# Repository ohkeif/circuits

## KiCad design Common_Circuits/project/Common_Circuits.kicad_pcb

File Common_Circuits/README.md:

# Common Circuits Keychain

Did you visit common circuits in Atlanta? And did you perhaps find yourself with a commemorative keychain accessory circuit board? After admiring the that commemorative keychain accessory circuit board for it's thoughtfulness, uniqueness, and clearly creative designer  - did you find yourself in a state of confounded intrigue as to the potential operation of the CKACB (commemorative keychain accessory circuit board)? Well you may be alone. Not that you are weird or slow or anything. It's just that I only made a few of these things...and I assume most people find them to be such a fashionable accessory, they may not even stop to think about the wonders that lie within the traces of their flashy keychain...but not you, you curious fellow. 

## What Dis Do?

All shall be revealed in due time...   

And that time is now. It's a synth. I mean it was pretty obvious to be honest..if you think about it. It's not like the event was for farming equipment or something. Then it maybe I could let it slide that you thought this was some sort of sprinkler timer. Or a controller to a door that automatically opens at sunrise to let the chickens out. The event was like 90% music oriented. You clearly already knew this. You are smart. Smart and Kind. And are just patiently waiting for the instructions on how do make it do a thing. The thing you knew it could do all along. Deep in your heart. And for that, I applaud you. And wait shall you no more!  

## But, I am not a Circuit Builder

Do not worry yourself with temporary concerns. And until you start on your learning journey, the CKACB will serve as a stylish keepsake of a truly memorable and life changing event for you. 

## BOM (Bill of Materials)

| Qty              | Reference | Value |
| :---------------- | :------: | ----: |
| 1	|C1	             | 0.01uf|
|1	|C2|	0.1uf|
|1	|C3	|10uf|
|1	|D1	|LED|
|2	|FREQ, PULSEWIDTH|	1M|
|1	|PWR	|DC IN|
|1	|OUT	|Audio Out
|2	|R1, R2	|1K|
|1	|R3	|10K|
|1	|R4	|4.7K|
|1	|SW2	|ON/OFF|
|2	|U1, U2	|LM555|
|1	|VOLUME	|5K|

## Stepped Tone Generator

This circuit is based off Forest Mims III Stepped Tone Generator circuit. It bleeps, bloops, and otherwise generates 8-bit console sounds. Sounds like high pitched zipping lasers and spacey distorted rocket arcade engine sounds. The circuit consists of two of the ubiquitous 8-pin DIP IC, the 555 timer, and an assortment of resistors and capacitors. In operation, the first timer is wired as an astable multivibrator that acts as a frequency oscillator. The second is set up as a monostable multivibrator that acts as the pulse width modulation of the firs timer. In other words, the oscillator (555 timer 1) drives the monostable (555 timer 2), which emits square output pulses with a duration controlled by the pulse width potentiometer. The resulting stepped tones almost sound like magic as they jump through lo-fi notes similar to chromatic rising and falling of keys on a keyboard.

## Assembly Instructions
Organize all your components to match up with the BOM to ensure you have everything you need to get started! Begin placing all the components onto the top side of the board with their legs poking through to the other side. 

Looking at the capacitors, C1 is marked with "103", where C2 is marked with "104". These numbers equate to the capacitance values, 0.01uf and 0.1uf respectively. 
C3 is an electrolytic capacitor with a cylindrical shape. This capacitor is polarized, meaning it has a positive and negative side. Find the negative side with the white stripe and place it accordingly on the board. 

### Electrolytic Capacitor Polarity

R1 and R2 are both 1k ohm resistors with the color code: Brown, Black, Red. R1 acts as a current limiter for the LED. R2 and the Frequency potentiometer controls the frequency of the audio oscillator. R3 and R4 along with the 10uf electrolytic capacitor form a low-pass filter that cut's high end artifacts from the audio output. Pulse Width controls the output pulse duration of the monostable multivibrator. And it is possible to add a mono jack onto pin 5 of each 555 chip to enable CV (control voltage) inputs for both controls.

Solder the IC socket with the correct orientation onto the board. Keep note of the notch on one end. Insert the IC into the IC socket staying consistent with the notch. Or don't use a socket. Just be careful and give the chip some time to cool off between soldering pins if soldering sans socket. 

### IC and IC Socket

Finally, obtain some spools of wire (20-24 gauge stranded core) and wire up the potentiometers, switches and power connections. To keep things organized, it may help to use green wire for ground connections, red wire for 9v connections, and yellow wire for audio connections. 

Now you can tape down all the components and flip over the board to solder everything up! 

### Schematic

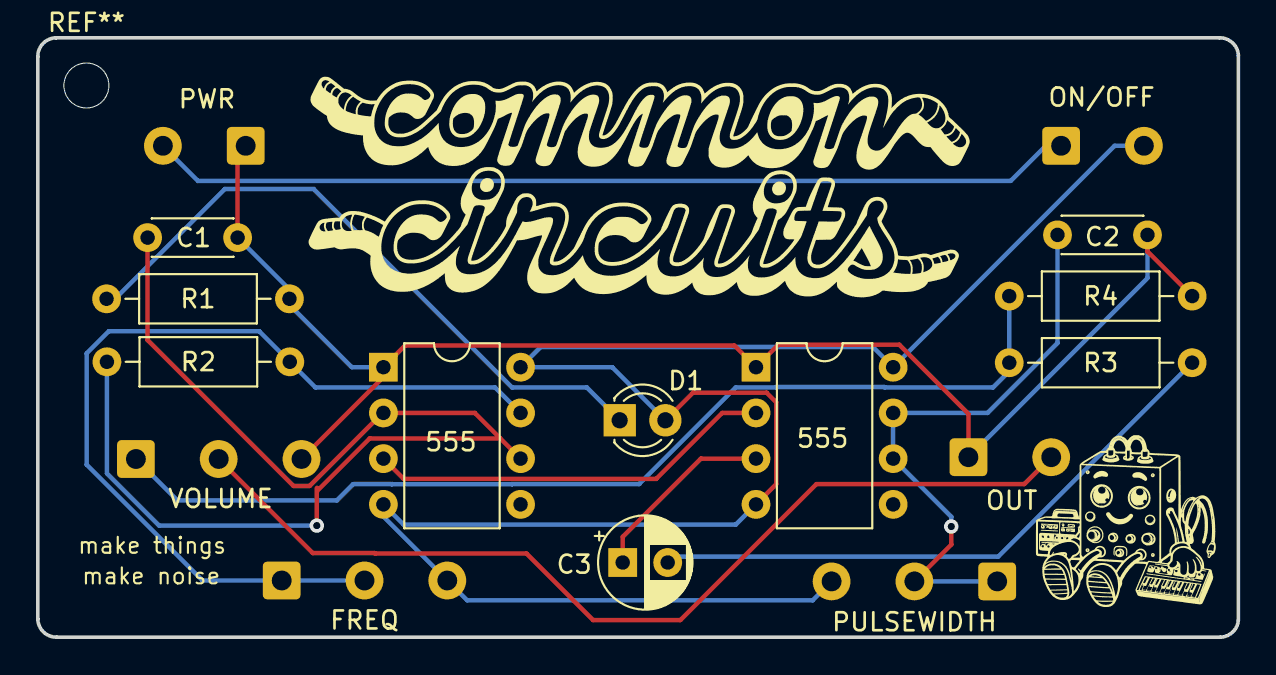
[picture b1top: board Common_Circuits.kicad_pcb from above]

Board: 2 copper layers, 66.7 x 33.3 mm, 16 parts (0 on the bottom side), 12 nets.

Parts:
C1: 0.01uf; C_Disc_D4.3mm_W1.9mm_P5.00mm
C2: 0.1uf; C_Disc_D4.3mm_W1.9mm_P5.00mm
C3: 10uf; CP_Radial_D5.0mm_P2.50mm
D1: LED; LED_D3.0mm
FREQ: 1M; SolderWire-0.5sqmm_1x03_P4.6mm_D0.9mm_OD2.1mm
ON/OFF: ON/OFF; SolderWire-0.5sqmm_1x02_P4.6mm_D0.9mm_OD2.1mm
OUT: Audio Out; SolderWire-0.5sqmm_1x02_P4.6mm_D0.9mm_OD2.1mm
PULSEWIDTH: 1M; SolderWire-0.5sqmm_1x03_P4.6mm_D0.9mm_OD2.1mm
PWR: DC IN; SolderWire-0.5sqmm_1x02_P4.6mm_D0.9mm_OD2.1mm
R1, R2: 1K; R_Axial_DIN0207_L6.3mm_D2.5mm_P10.16mm_Horizontal
R3: 10K; R_Axial_DIN0207_L6.3mm_D2.5mm_P10.16mm_Horizontal
R4: 4.7K; R_Axial_DIN0207_L6.3mm_D2.5mm_P10.16mm_Horizontal
U1, U2: 555; DIP-8_W7.62mm
VOLUME: 5K; SolderWire-0.5sqmm_1x03_P4.6mm_D0.9mm_OD2.1mm

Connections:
+9V: ON/OFF.1 (A), PWR.2
/PWR: D1.2 (A), FREQ.3, ON/OFF.2 (B), PULSEWIDTH.3, U1.4 (R), U1.8 (VCC), U2.4 (R), U2.8 (VCC)
GND: C1.1, C2.1, OUT.S, PWR.1, R1.1, R4.1, U1.1 (GND), U2.1 (GND), VOLUME.3
unnamed: C1.2, R2.2, U1.2 (TR), U1.6 (THR)
unnamed: D1.1 (K), R1.2
unnamed: FREQ.1, FREQ.2, R2.1, U1.7 (DIS)
unnamed: OUT.T, VOLUME.2
unnamed: C2.2, PULSEWIDTH.1, PULSEWIDTH.2, U2.6 (THR), U2.7 (DIS)
unnamed: C3.2, R3.1
unnamed: R3.2, R4.2, VOLUME.1
unnamed: U1.3 (Q), U2.2 (TR)
unnamed: C3.1, U2.3 (Q)

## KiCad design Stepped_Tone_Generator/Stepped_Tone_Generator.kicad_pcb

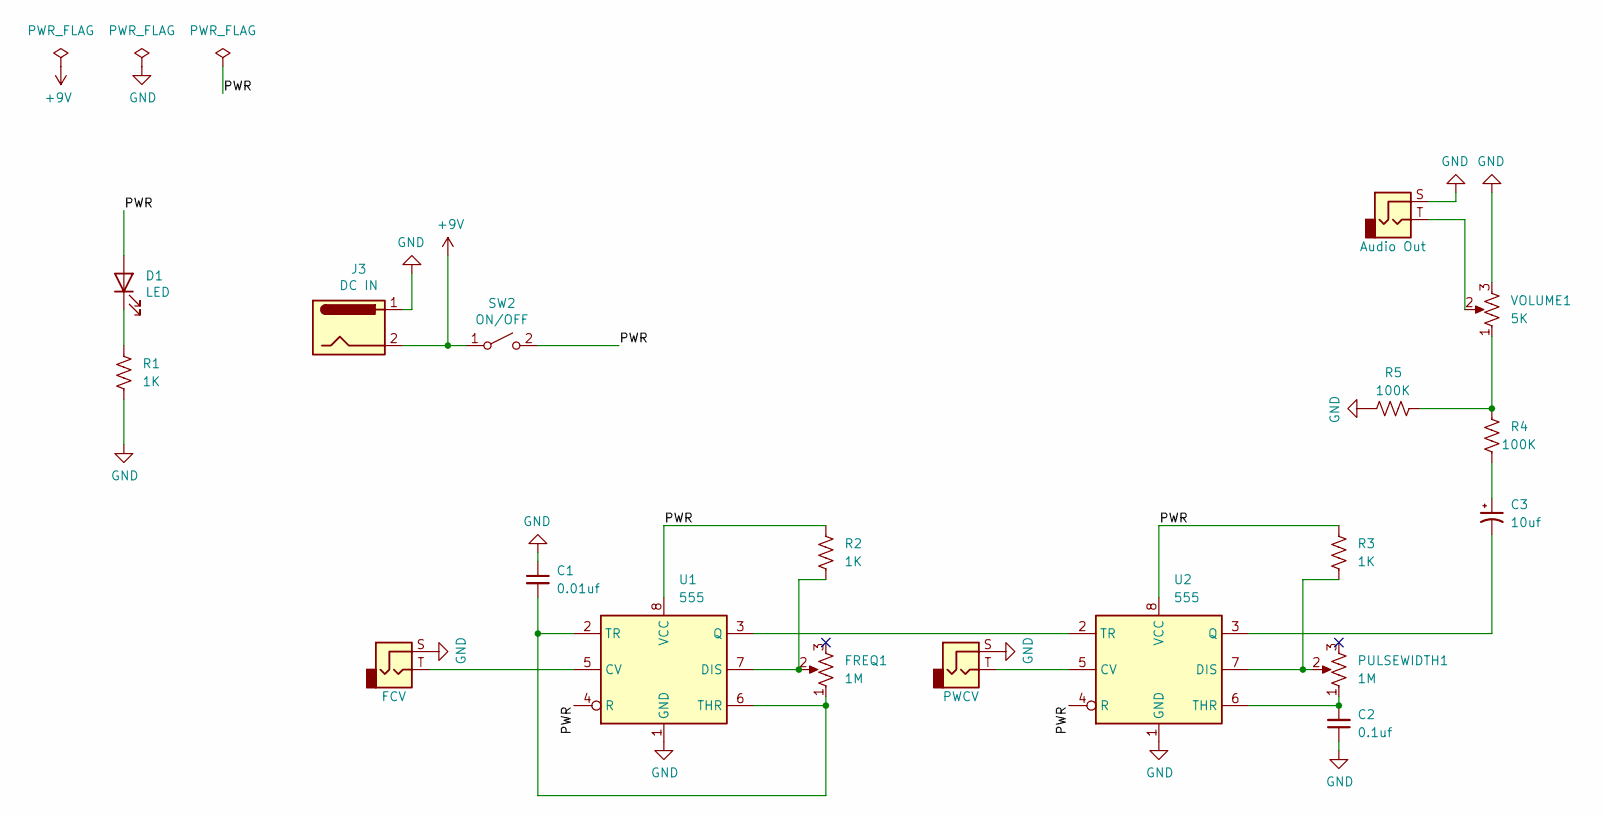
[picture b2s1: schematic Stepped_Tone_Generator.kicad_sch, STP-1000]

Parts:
C1: 0.01uf; C_Disc_D4.3mm_W1.9mm_P5.00mm
C2: 0.1uf; C_Disc_D4.3mm_W1.9mm_P5.00mm
C3: 10uf; CP_Radial_D5.0mm_P2.50mm
D1: LED; LED_D3.0mm
FREQ1: 1M; SolderWire-0.5sqmm_1x03_P4.6mm_D0.9mm_OD2.1mm
J1: FCV; SolderWire-0.5sqmm_1x02_P4.6mm_D0.9mm_OD2.1mm
J2: PWCV; SolderWire-0.5sqmm_1x02_P4.6mm_D0.9mm_OD2.1mm
J3: DC IN; SolderWire-0.5sqmm_1x02_P4.6mm_D0.9mm_OD2.1mm
J4: Audio Out; SolderWire-0.5sqmm_1x02_P4.6mm_D0.9mm_OD2.1mm
PULSEWIDTH1: 1M; SolderWire-0.5sqmm_1x03_P4.6mm_D0.9mm_OD2.1mm
R1, R2, R3: 1K; R_Axial_DIN0207_L6.3mm_D2.5mm_P10.16mm_Horizontal
R4, R5: 100K; R_Axial_DIN0207_L6.3mm_D2.5mm_P10.16mm_Horizontal
SW2: ON/OFF; SolderWire-0.5sqmm_1x02_P4.6mm_D0.9mm_OD2.1mm
U1, U2: 555; DIP-8_W7.62mm
VOLUME1: 5K; SolderWire-0.5sqmm_1x03_P4.6mm_D0.9mm_OD2.1mm

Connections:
+9V: J3.2, SW2.1 (A)
/PWR: D1.2 (A), R2.2, R3.2, SW2.2 (B), U1.4 (R), U1.8 (VCC), U2.4 (R), U2.8 (VCC)
GND: C1.1, C2.1, J1.S, J2.S, J3.1, J4.S, R1.1, R5.1, U1.1 (GND), U2.1 (GND), VOLUME1.3
unnamed: C1.2, FREQ1.1, U1.2 (TR), U1.6 (THR)
unnamed: C2.2, PULSEWIDTH1.1, U2.6 (THR)
unnamed: C3.1, R4.1
unnamed: C3.2, U2.3 (Q)
unnamed: D1.1 (K), R1.2
unnamed: FREQ1.2, R2.1, U1.7 (DIS)
unnamed: J1.T, U1.5 (CV)
unnamed: J2.T, U2.5 (CV)
unnamed: J4.T, VOLUME1.2
unnamed: PULSEWIDTH1.2, R3.1, U2.7 (DIS)
unnamed: R4.2, R5.2, VOLUME1.1
unnamed: U1.3 (Q), U2.2 (TR)

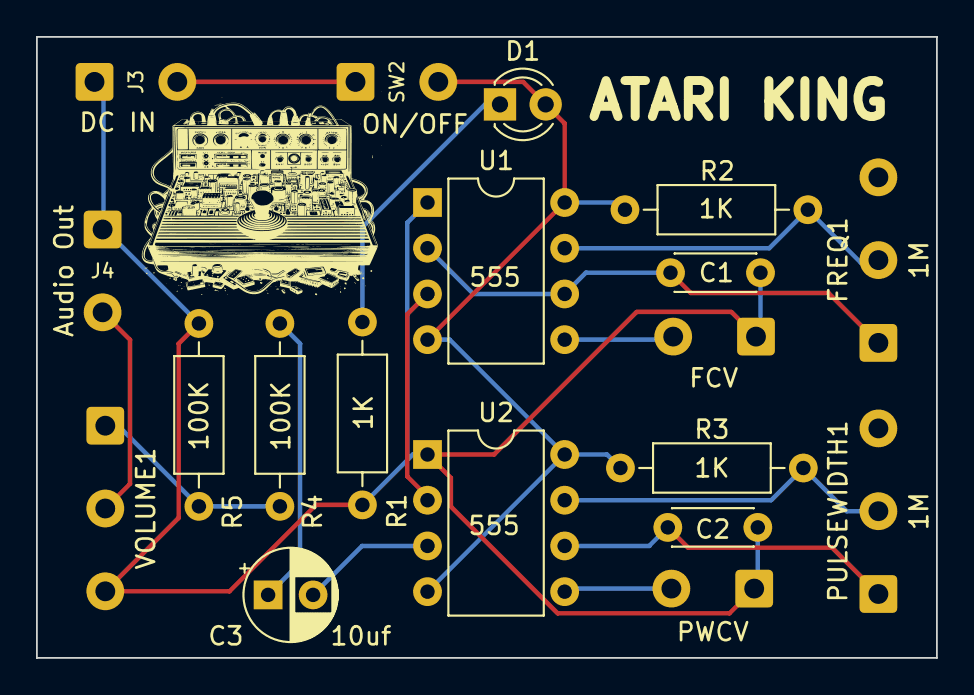
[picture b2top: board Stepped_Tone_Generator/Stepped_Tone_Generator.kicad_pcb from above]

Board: 2 copper layers, 50.0 x 34.5 mm, 19 parts (0 on the bottom side), 15 nets.

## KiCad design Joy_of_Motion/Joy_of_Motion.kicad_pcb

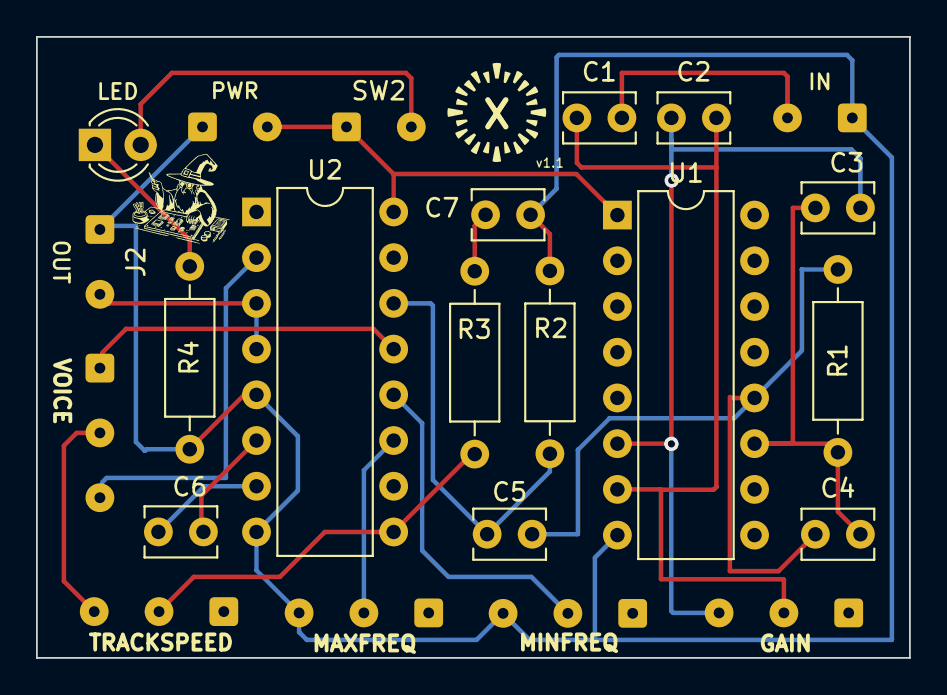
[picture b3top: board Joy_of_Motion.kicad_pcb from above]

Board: 2 copper layers, 48.5 x 34.5 mm, 23 parts (0 on the bottom side), 20 nets.

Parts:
C1, C3, C5, C6, C7: 0.1uf; C_Disc_D3.8mm_W2.6mm_P2.50mm
C2, C4: 47pf; C_Disc_D3.8mm_W2.6mm_P2.50mm
GAIN1: 1M; SolderWire-0.1sqmm_1x03_P3.6mm_D0.4mm_OD1mm
J1: IN; SolderWire-0.1sqmm_1x02_P3.6mm_D0.4mm_OD1mm
J2: OUT; SolderWire-0.1sqmm_1x02_P3.6mm_D0.4mm_OD1mm
LED: LED; LED_D3.0mm
MAXFREQ1: 1M; SolderWire-0.1sqmm_1x03_P3.6mm_D0.4mm_OD1mm
MINFREQ1: 1M; SolderWire-0.1sqmm_1x03_P3.6mm_D0.4mm_OD1mm
PWR: DC IN; SolderWire-0.1sqmm_1x02_P3.6mm_D0.4mm_OD1mm
R1, R2, R3: 100K; R_Axial_DIN0207_L6.3mm_D2.5mm_P10.16mm_Horizontal
R4: 1k; R_Axial_DIN0207_L6.3mm_D2.5mm_P10.16mm_Horizontal
SW1: VOICE; SolderWire-0.1sqmm_1x03_P3.6mm_D0.4mm_OD1mm
SW2: ON/OFF; SolderWire-0.1sqmm_1x02_P3.6mm_D0.4mm_OD1mm
TRKSPD1: 1M; SolderWire-0.1sqmm_1x03_P3.6mm_D0.4mm_OD1mm
U1: 4049; DIP-16_W7.62mm
U2: 4046; DIP-16_W7.62mm

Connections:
+9V: PWR.2, SW2.1 (A), U1.8 (VSS), U2.16 (VDD)
/PWR: LED.2 (A), SW2.2 (B)
GND: C5.1, J1.S, J2.S, MAXFREQ1.3, MINFREQ1.3, PWR.1, R3.1, R4.2, U1.1 (VCC), U2.5 (Inh), U2.8 (VSS)
unnamed: C1.1, C2.2, GAIN1.2, U1.7
unnamed: C1.2, J1.T
unnamed: C2.1, C3.2, GAIN1.3, U1.6
unnamed: C3.1, C4.2, R1.2, U1.11
unnamed: C4.1, C6.2, R1.1, U1.12
unnamed: C5.2, R2.2
unnamed: C6.1, R3.2, U2.14 (SigIn)
unnamed: C7.1, U2.7 (C2)
unnamed: C7.2, U2.6 (C1)
unnamed: LED.1 (K), R4.1
unnamed: J2.T, U2.3 (RefIn), U2.4 (FOUT)
unnamed: MAXFREQ1.2, U2.11 (R1)
unnamed: MINFREQ1.2, U2.12 (R2)
unnamed: R2.1, TRKSPD1.2, U2.9 (VCOin)
unnamed: SW1.1 (A), U2.13 (PC2)
unnamed: SW1.2 (B), TRKSPD1.3
unnamed: SW1.3 (C), U2.2 (PC1)

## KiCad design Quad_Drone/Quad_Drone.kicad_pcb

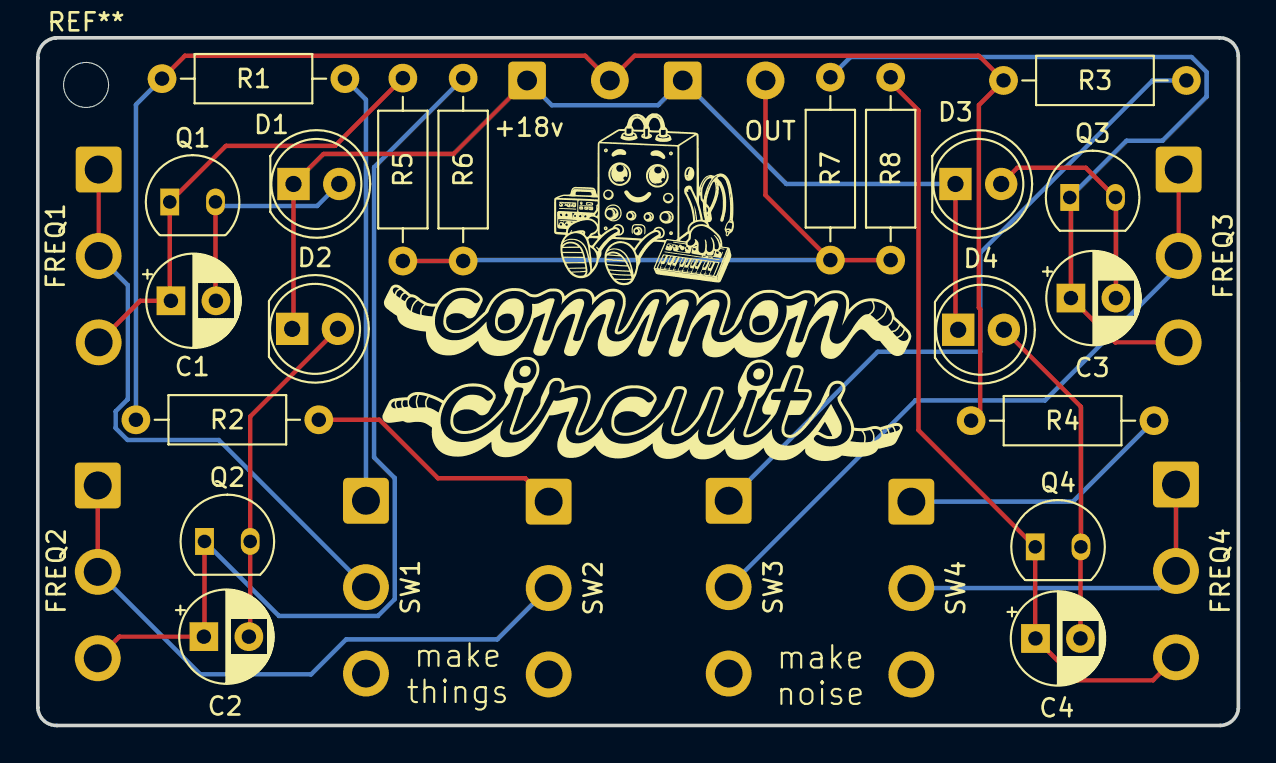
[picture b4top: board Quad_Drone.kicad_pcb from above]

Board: 2 copper layers, 66.7 x 38.2 mm, 30 parts (0 on the bottom side), 19 nets.

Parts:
+18v: DC IN; SolderWire-0.5sqmm_1x02_P4.6mm_D0.9mm_OD2.1mm
C1, C2: 10uf; CP_Radial_D5.0mm_P2.50mm
C3: 4.7uf; CP_Radial_D5.0mm_P2.50mm
C4: 2.2uf; CP_Radial_D5.0mm_P2.50mm
D1, D2, D3, D4: LED; LED_D5.0mm
FREQ1, FREQ2, FREQ3, FREQ4: 10k; SolderWire-0.75sqmm_1x03_P4.8mm_D1.25mm_OD2.3mm
OUT: OUT; SolderWire-0.5sqmm_1x02_P4.6mm_D0.9mm_OD2.1mm
Q1, Q2, Q3, Q4: 2N3904; TO-92-2-modified
R1, R2, R3, R4: 1K; R_Axial_DIN0207_L6.3mm_D2.5mm_P10.16mm_Horizontal
R5, R6, R7, R8: 100K; R_Axial_DIN0207_L6.3mm_D2.5mm_P10.16mm_Horizontal
SW1, SW2, SW3, SW4: ON/OFF; SolderWire-0.75sqmm_1x03_P4.8mm_D1.25mm_OD2.3mm

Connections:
+9V: +18v.2, R1.1, R2.1, R3.1, R4.1
GND: +18v.1, D1.1 (K), D2.1 (K), D3.1 (K), D4.1 (K), OUT.1
unnamed: C1.1, FREQ1.3, Q1.1 (E), R5.1
unnamed: C1.2, D1.2 (A), Q1.3 (C)
unnamed: C2.1, FREQ2.3, Q2.1 (E), R6.1
unnamed: C2.2, D2.2 (A), Q2.3 (C)
unnamed: C3.1, FREQ3.3, Q3.1 (E), R7.1
unnamed: C3.2, D3.2 (A), Q3.3 (C)
unnamed: C4.1, FREQ4.3, Q4.1 (E), R8.1
unnamed: C4.2, D4.2 (A), Q4.3 (C)
unnamed: FREQ1.1, FREQ1.2, SW1.2 (B)
unnamed: FREQ2.1, FREQ2.2, SW2.2 (B)
unnamed: FREQ3.1, FREQ3.2, SW3.2 (B)
unnamed: FREQ4.1, FREQ4.2, SW4.2 (B)
unnamed: OUT.T, R5.2, R6.2, R7.2, R8.2
unnamed: R1.2, SW1.1 (A)
unnamed: R2.2, SW2.1 (A)
unnamed: R3.2, SW3.1 (A)
unnamed: R4.2, SW4.1 (A)

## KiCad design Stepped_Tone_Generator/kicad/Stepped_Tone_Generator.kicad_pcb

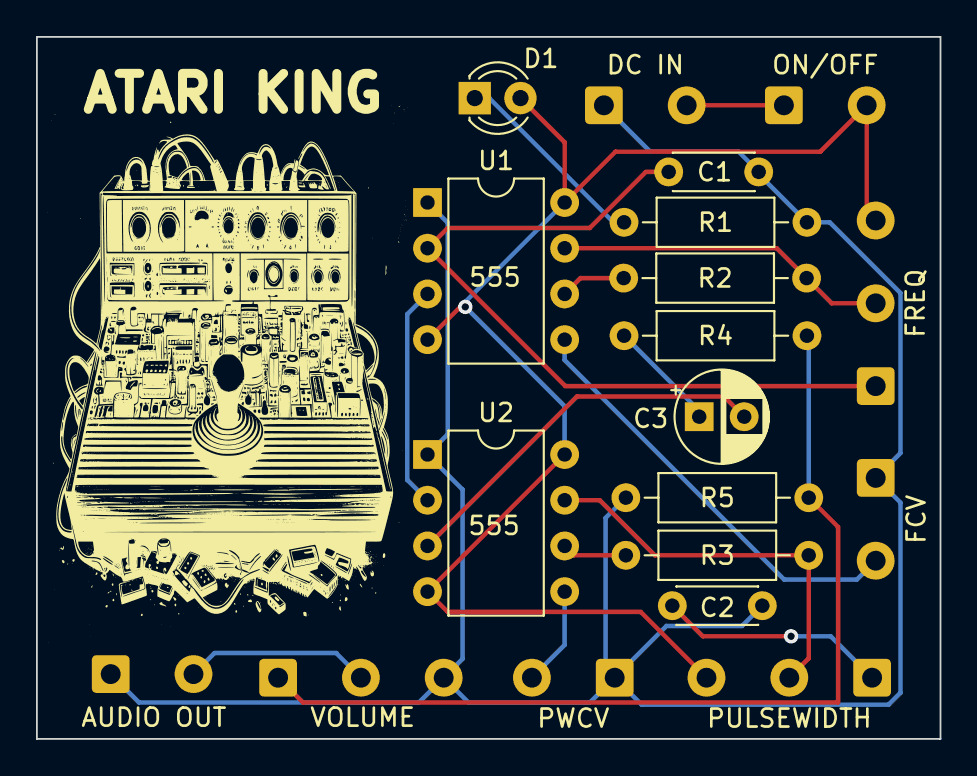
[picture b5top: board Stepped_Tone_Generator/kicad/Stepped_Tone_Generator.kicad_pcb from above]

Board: 2 copper layers, 50.2 x 39.0 mm, 19 parts (0 on the bottom side), 17 nets.

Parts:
AUDIO OUT: AUDIO OUT; SolderWire-0.5sqmm_1x02_P4.6mm_D0.9mm_OD2.1mm
C1: .01uf; C_Disc_D4.3mm_W1.9mm_P5.00mm
C2: .1uf; C_Disc_D4.3mm_W1.9mm_P5.00mm
C3: 10uf; CP_Radial_D5.0mm_P2.50mm
D1: LED; LED_D3.0mm
DC IN: DC IN; SolderWire-0.5sqmm_1x02_P4.6mm_D0.9mm_OD2.1mm
FCV: FCV; SolderWire-0.5sqmm_1x02_P4.6mm_D0.9mm_OD2.1mm
FREQ: 1M; SolderWire-0.5sqmm_1x03_P4.6mm_D0.9mm_OD2.1mm
ON/OFF: ON/OFF; SolderWire-0.5sqmm_1x02_P4.6mm_D0.9mm_OD2.1mm
PULSEWIDTH: 1M; SolderWire-0.5sqmm_1x03_P4.6mm_D0.9mm_OD2.1mm
PWCV: PWCV; SolderWire-0.5sqmm_1x02_P4.6mm_D0.9mm_OD2.1mm
R1, R2, R3: 1K; R_Axial_DIN0207_L6.3mm_D2.5mm_P10.16mm_Horizontal
R4: 10K; R_Axial_DIN0207_L6.3mm_D2.5mm_P10.16mm_Horizontal
R5: 4.7K; R_Axial_DIN0207_L6.3mm_D2.5mm_P10.16mm_Horizontal
U1, U2: 555; DIP-8_W7.62mm
VOLUME: 5K; SolderWire-0.5sqmm_1x03_P4.6mm_D0.9mm_OD2.1mm

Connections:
+9V: DC IN.2, ON/OFF.1 (A)
/PWR: D1.2 (A), FREQ.3, ON/OFF.2 (B), PULSEWIDTH.3, U1.4 (R), U1.8 (VCC), U2.4 (R), U2.8 (VCC)
GND: AUDIO OUT.S, C1.1, C2.1, DC IN.1, FCV.S, PWCV.S, R1.1, R5.1, U1.1 (GND), U2.1 (GND), VOLUME.3
unnamed: C1.2, FREQ.1, U1.2 (TR)
unnamed: C3.1, R4.1
unnamed: C3.2, U2.3 (Q)
unnamed: D1.1 (K), R1.2
unnamed: FREQ.2, R2.2, U1.7 (DIS)
unnamed: FCV.T, U1.5 (CV)
unnamed: PWCV.T, U2.5 (CV)
unnamed: AUDIO OUT.T, VOLUME.2
unnamed: C2.2, PULSEWIDTH.1
unnamed: PULSEWIDTH.2, R3.2, U2.7 (DIS)
unnamed: R4.2, R5.2, VOLUME.1
unnamed: U1.3 (Q), U2.2 (TR)
unnamed: R2.1, U1.6 (THR)
unnamed: R3.1, U2.6 (THR)

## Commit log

2024-07-23 send it
2024-07-23 PLL Images
2024-07-23 images
2024-07-23 adding PLL footprints
2024-07-23 adding wizards
2024-07-23 adding silkscreen images
2024-07-24 atari king layouts
2024-07-24 remove backups
2024-07-24 cleanup
2024-10-13 atari_king
2024-10-13 adding BOMs
2024-10-16 Common Circuits
2024-10-16 CC Readme
2024-10-31 adding README and images
2024-10-31 README.md
2025-10-04 moar circuits
2025-10-04 Quad_Drone
2025-10-04 drone reademe
2025-10-04 quad_drone assembly instructions
2025-10-04 Updating READMEs
2025-10-04 Updating readme
2025-10-04 adding schematic
